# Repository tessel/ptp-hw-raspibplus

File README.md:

**[UNMAINTAINED] This library does not have a maintainer. The source code and repository will be kept at this URL indefinitely. If you'd like to help maintain this codebase, create an issue on this repo explaining why you'd like to become a maintainer and tag @tessel/maintainers in the body.**

ptp-hw-raspibplus
==================
Hardware adaptor to allow Tessel modules to be used with a Raspberry Pi B+ in conjunction with the Portable Tessel Platform (PTP).

Designs in KiCad.

### License

Copyright 2014 Technical Machine, Inc.
CC-BY-SA

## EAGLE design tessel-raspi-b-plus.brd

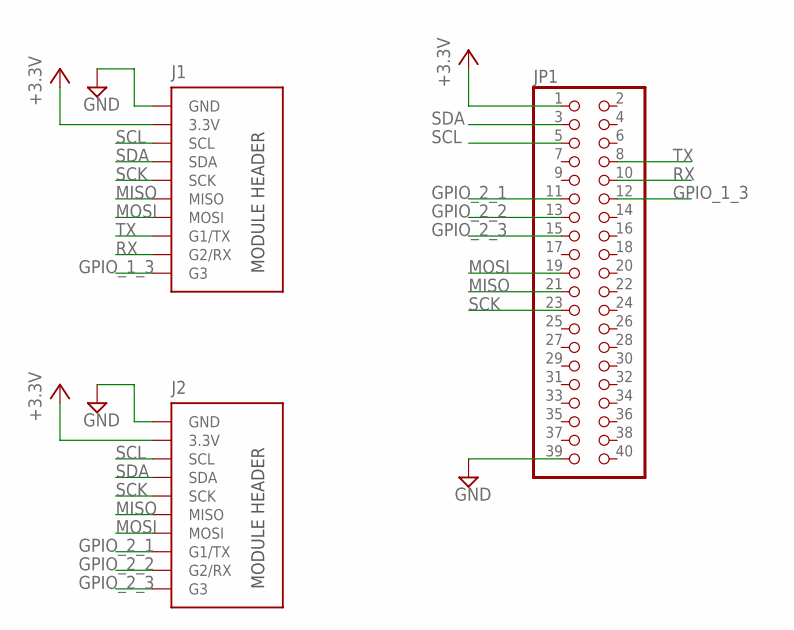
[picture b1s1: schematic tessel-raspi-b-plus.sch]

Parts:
J1, J2: MODULE_HEADER_MODULEDEFAULT; MODULE_HEADER_MODULE
JP1: PINHD-2X20; 2X20

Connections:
3.3V: J2.3.3V
+3.3V: J1.3.3V, JP1.1
GND: J1.GND, J2.GND
GPIO_1_3: J1.G3, JP1.12
GPIO_2_1: J2.G1/TX, JP1.11
GPIO_2_2: J2.G2/RX, JP1.13
GPIO_2_3: J2.G3, JP1.15
MISO: J1.MISO, J2.MISO, JP1.21
MOSI: J1.MOSI, J2.MOSI, JP1.19
RX: J1.G2/RX, JP1.10
SCK: J1.SCK, J2.SCK, JP1.23
SCL: J1.SCL, J2.SCL, JP1.5
SDA: J1.SDA, J2.SDA, JP1.3
TX: J1.G1/TX, JP1.8

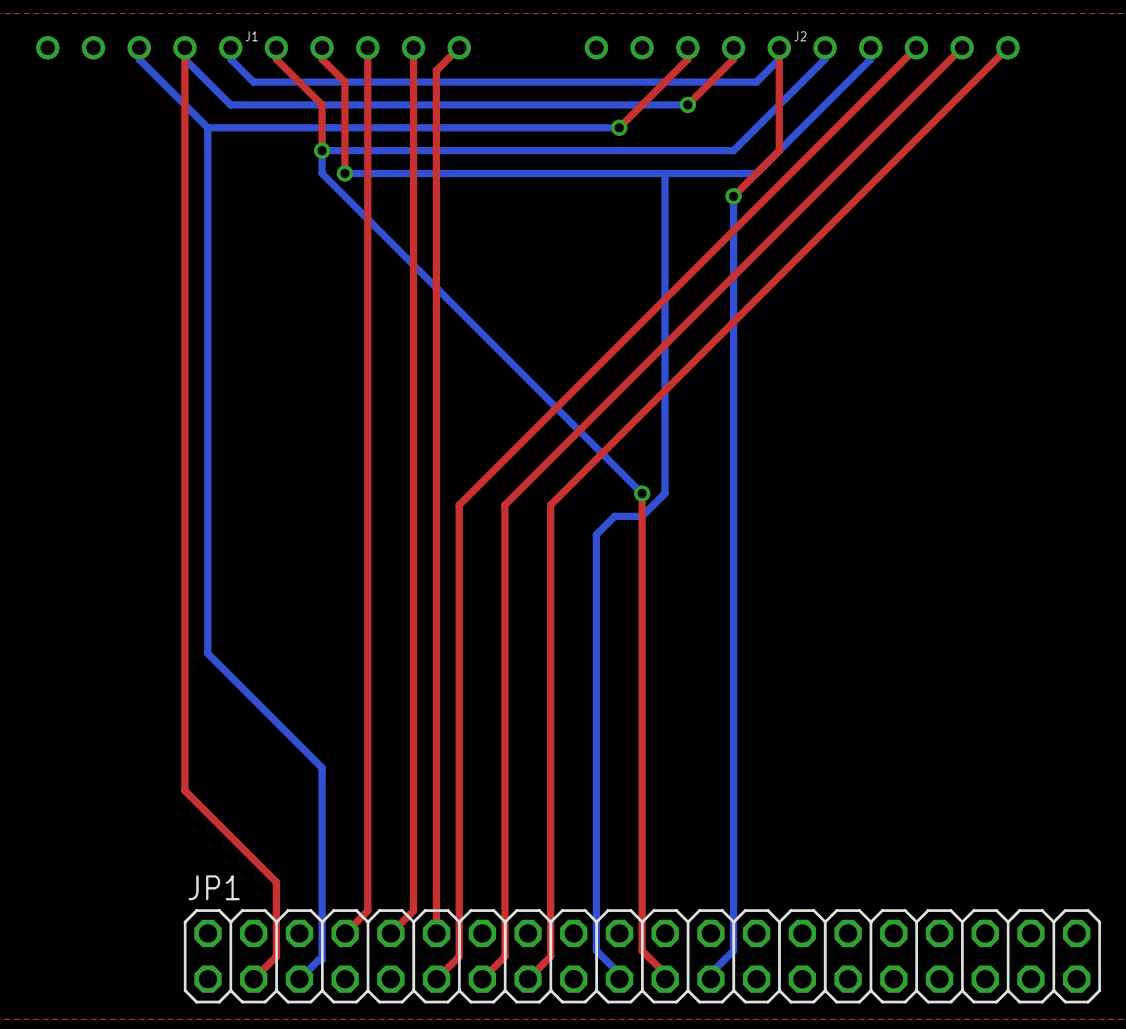
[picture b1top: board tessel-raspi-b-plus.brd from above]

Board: 2 copper layers, 3 parts (0 on the bottom side), 13 nets.

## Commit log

2014-08-20 raspi module for ptp
2014-08-22 added silkscreen text
    fixed repo
    Create README.md
2014-09-05 update readme, license
2014-09-05 wipe for kicad
2014-09-05 started kicad project, schem
2014-09-05 parts in schematic, gotta do footprints
2014-09-05 schematic first pass
2014-09-05 netlist, annotation
2014-09-05 first pass component file
2014-09-05 board file exists, components are all on it...rpi silk is no good
2014-09-05 better silk for rpi header
2014-09-05 close to refresh
2014-09-05 note about 3.3 rail, updated silk
2014-09-05 ...at least the board has mount holes now
2014-09-05 how did the pcb files not get added?
2014-09-05 positioning things is hard
2014-09-05 started routing, decided to pursue parallel instead
2014-09-05 mostly happy. power and ground left.
2014-09-06 really really close
2014-09-06 stupid not-polygons are stupid
2014-09-06 silk tweaks to refdes
2014-09-06 10mil pour clear
2014-09-06 drc pass ...stupid vias
2014-09-06 pour tweaks
2014-09-06 gerbers
2014-09-06 project saved, closed, sent for review
2014-09-06 schem as postscript
2014-09-08 added ptp rpib+ logo, board dimensions, updated gerbers
2014-09-08 gerber zip
